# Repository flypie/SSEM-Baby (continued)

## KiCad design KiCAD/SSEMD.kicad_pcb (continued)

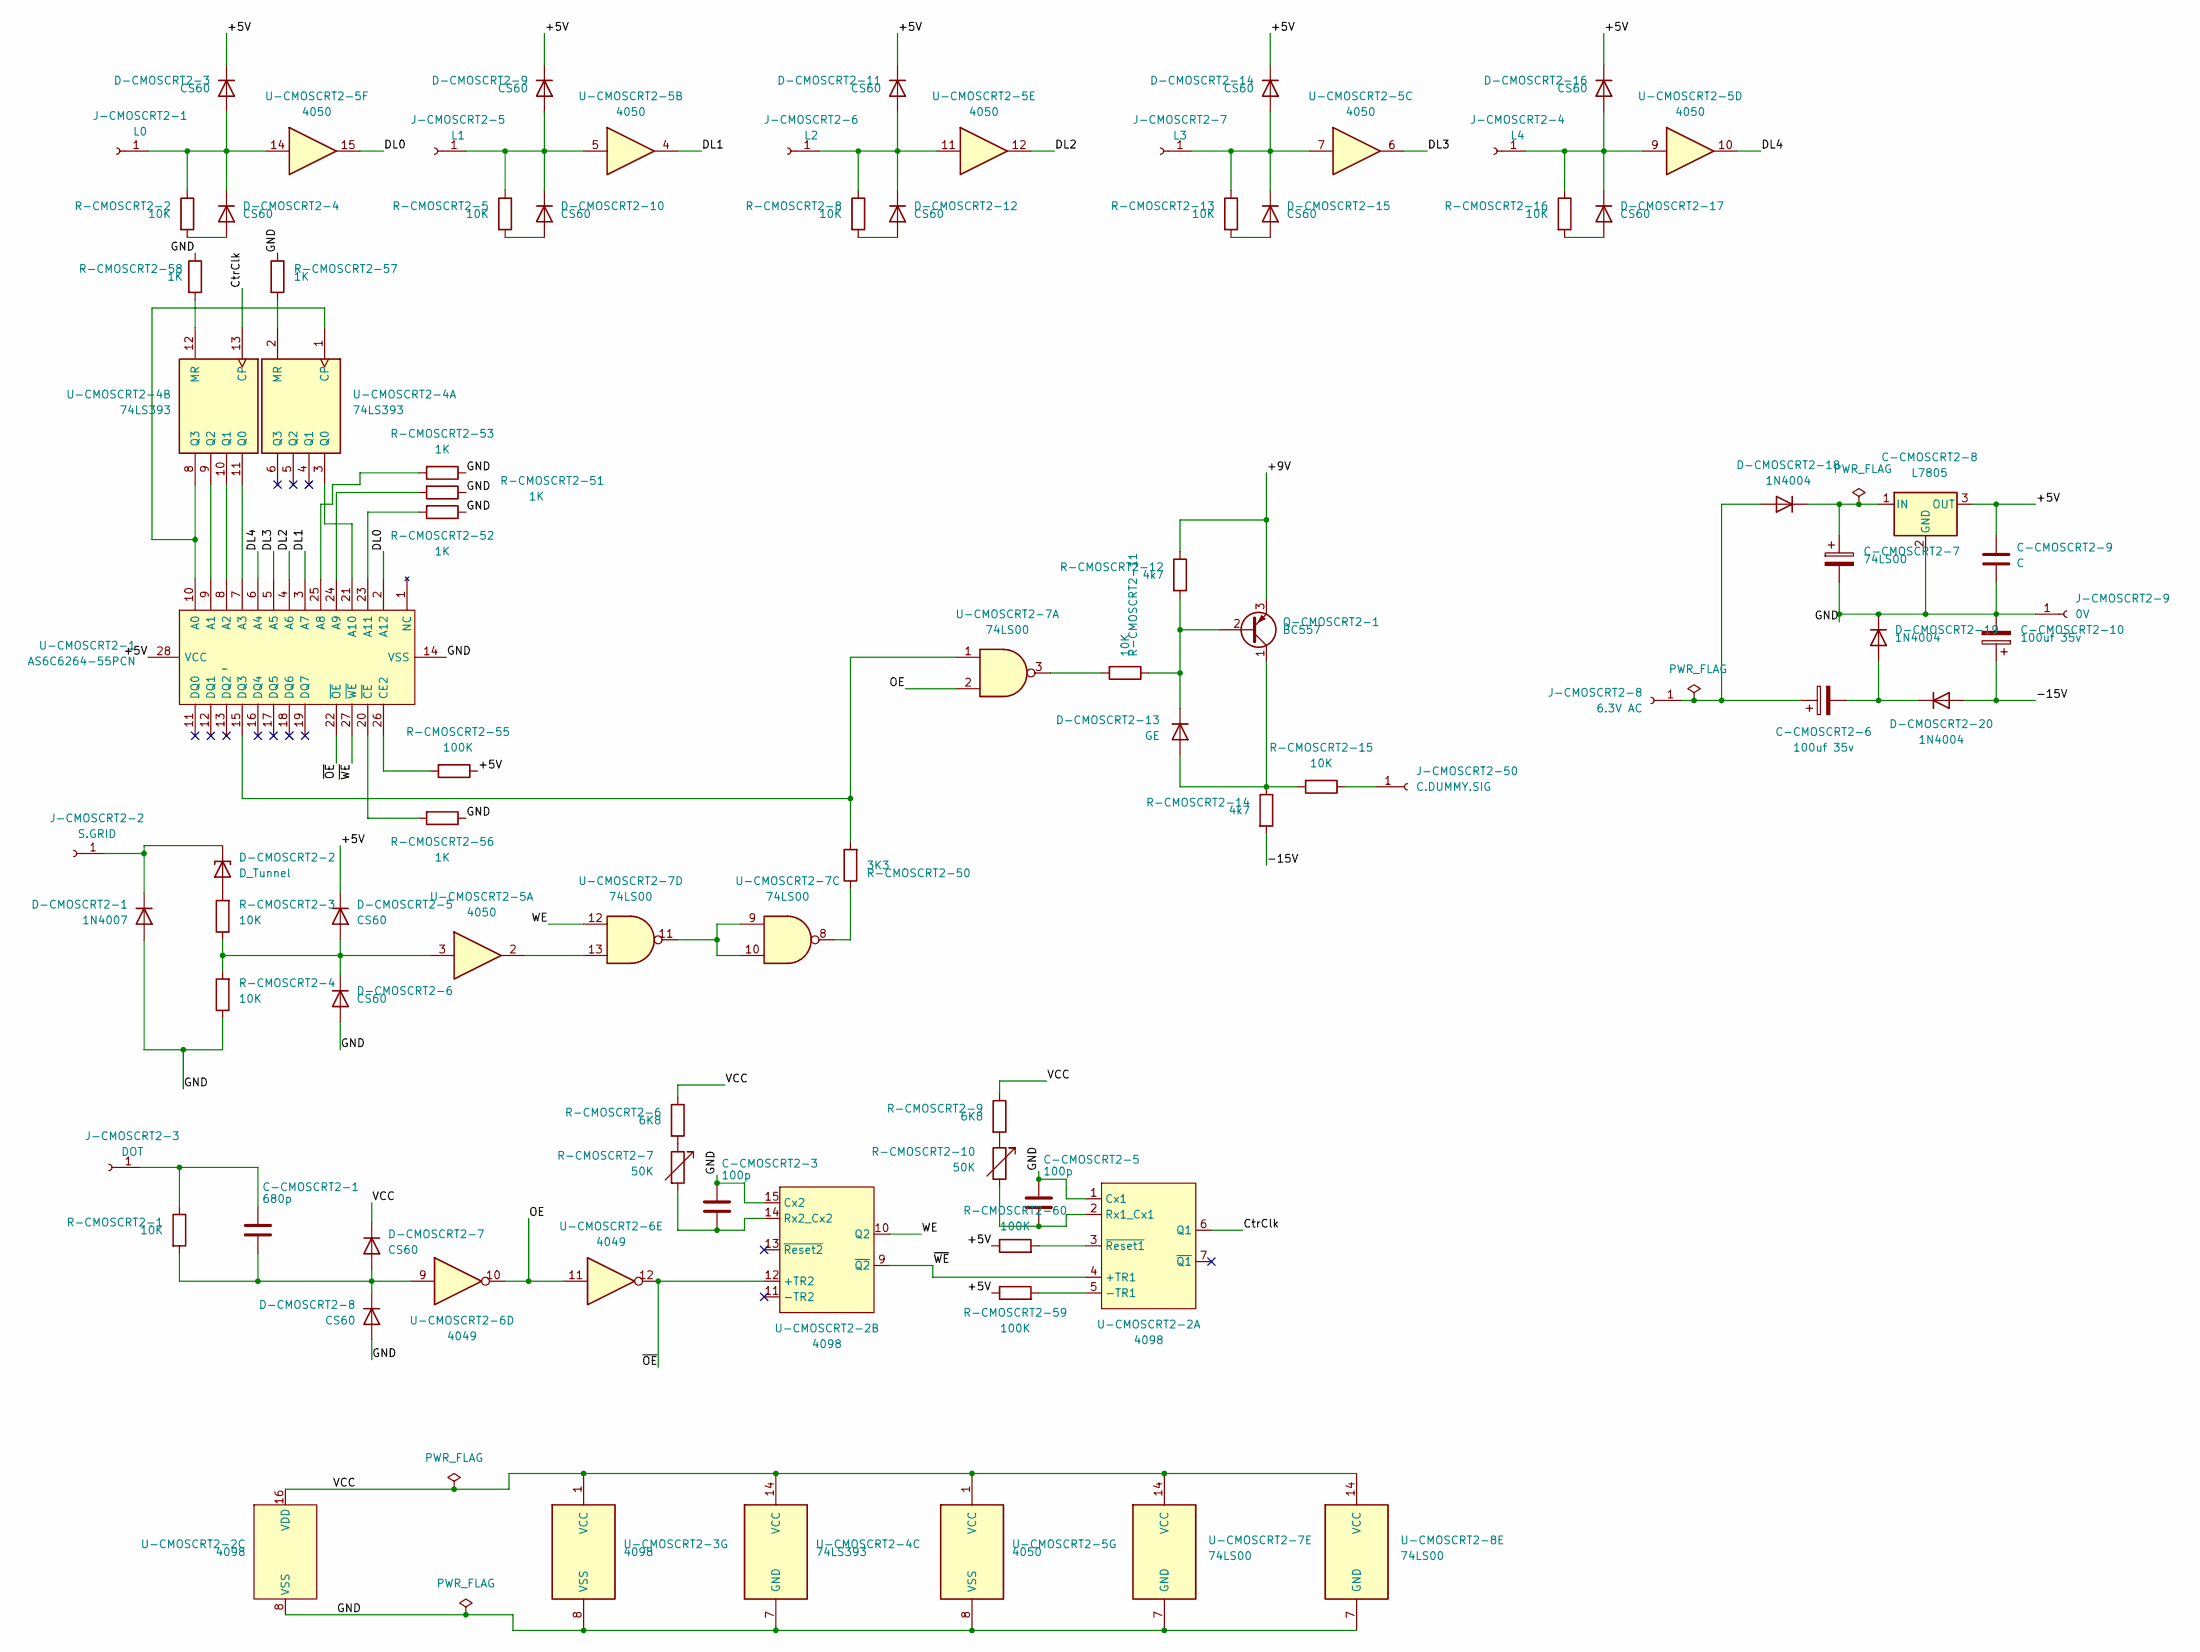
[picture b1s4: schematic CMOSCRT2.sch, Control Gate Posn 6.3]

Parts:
C-CMOSCRT2-1: 680p; C_Disc_D7.5mm_W5.0mm_P5.00mm
C-CMOSCRT2-3, C-CMOSCRT2-5: 100p; C_Disc_D7.5mm_W5.0mm_P5.00mm
C-CMOSCRT2-6, C-CMOSCRT2-10: 100uf 35v; CP_Radial_D5.0mm_P2.50mm
C-CMOSCRT2-7: 74LS00; CP_Radial_D5.0mm_P2.50mm
C-CMOSCRT2-8: L7805; TO-220-3_Vertical
C-CMOSCRT2-9: C; C_Disc_D3.8mm_W2.6mm_P2.50mm
D-CMOSCRT2-1: 1N4007; D_DO-41_SOD81_P10.16mm_Horizontal
D-CMOSCRT2-2: D_Tunnel; D_DO-41_SOD81_P10.16mm_Horizontal
D-CMOSCRT2-3, D-CMOSCRT2-4, D-CMOSCRT2-5, D-CMOSCRT2-6, D-CMOSCRT2-7, D-CMOSCRT2-8, D-CMOSCRT2-9, D-CMOSCRT2-10, D-CMOSCRT2-11, D-CMOSCRT2-12, D-CMOSCRT2-14, D-CMOSCRT2-15, D-CMOSCRT2-16, D-CMOSCRT2-17: CS60; D_DO-41_SOD81_P10.16mm_Horizontal
D-CMOSCRT2-13: GE; D_DO-41_SOD81_P10.16mm_Horizontal
D-CMOSCRT2-18, D-CMOSCRT2-19, D-CMOSCRT2-20: 1N4004; D_DO-41_SOD81_P10.16mm_Horizontal
J-CMOSCRT2-1: L0; 242431
J-CMOSCRT2-2: S.GRID; 242431
J-CMOSCRT2-3: DOT; 242431
J-CMOSCRT2-4: L4; 242431
J-CMOSCRT2-5: L1; 242431
J-CMOSCRT2-6: L2; 242431
J-CMOSCRT2-7: L3; 242431
J-CMOSCRT2-8: 6.3V AC; 242431
J-CMOSCRT2-9: 0V; 242431
J-CMOSCRT2-50: C.DUMMY.SIG; 242431
Q-CMOSCRT2-1: BC557; TO-92_Inline
R-CMOSCRT2-1, R-CMOSCRT2-2, R-CMOSCRT2-3, R-CMOSCRT2-4, R-CMOSCRT2-5, R-CMOSCRT2-8, R-CMOSCRT2-11, R-CMOSCRT2-13, R-CMOSCRT2-15, R-CMOSCRT2-16: 10K; R_Axial_DIN0516_L15.5mm_D5.0mm_P5.08mm_Vertical
R-CMOSCRT2-6, R-CMOSCRT2-9: 6K8; R_Axial_DIN0516_L15.5mm_D5.0mm_P5.08mm_Vertical
R-CMOSCRT2-7, R-CMOSCRT2-10: 50K; Potentiometer_Omeg_PC16BU_Vertical
R-CMOSCRT2-12, R-CMOSCRT2-14: 4k7; R_Axial_DIN0516_L15.5mm_D5.0mm_P5.08mm_Vertical
R-CMOSCRT2-50: 3K3; R_Axial_DIN0516_L15.5mm_D5.0mm_P5.08mm_Vertical
R-CMOSCRT2-51, R-CMOSCRT2-52, R-CMOSCRT2-53, R-CMOSCRT2-56, R-CMOSCRT2-57, R-CMOSCRT2-58: 1K; R_Axial_DIN0516_L15.5mm_D5.0mm_P5.08mm_Vertical
R-CMOSCRT2-55, R-CMOSCRT2-59, R-CMOSCRT2-60: 100K; R_Axial_DIN0516_L15.5mm_D5.0mm_P5.08mm_Vertical
U-CMOSCRT2-1: AS6C6264-55PCN; DIP1524W51P254L3632H394Q28N; Manufacturer_Part_Number AS6C6264-55PCN; Mouser Part Number 913-AS6C6264-55PCN
U-CMOSCRT2-2: 4098; DIP-16_W7.62mm
U-CMOSCRT2-3: 4098; DIP-14_W7.62mm
U-CMOSCRT2-4: 74LS393; DIP-14_W7.62mm
U-CMOSCRT2-5: 4050; DIP-16_W7.62mm
U-CMOSCRT2-6: 4049; DIP-14_W7.62mm
U-CMOSCRT2-7, U-CMOSCRT2-8: 74LS00; DIP-14_W7.62mm

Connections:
/CMOSCRT2/+5V: C-CMOSCRT2-8.3 (OUT), C-CMOSCRT2-9.1, D-CMOSCRT2-3.1 (K), D-CMOSCRT2-5.1 (K), D-CMOSCRT2-9.1 (K), D-CMOSCRT2-11.1 (K), D-CMOSCRT2-14.1 (K), D-CMOSCRT2-16.1 (K), R-CMOSCRT2-55.1, R-CMOSCRT2-59.1, R-CMOSCRT2-60.1, U-CMOSCRT2-1.28 (VCC)
/CMOSCRT2/+9V: Q-CMOSCRT2-1.3 (E), R-CMOSCRT2-12.1
/CMOSCRT2/-15V: C-CMOSCRT2-10.1, D-CMOSCRT2-20.2 (A), R-CMOSCRT2-14.2
/CMOSCRT2/CtrClk: U-CMOSCRT2-2.6 (Q1), U-CMOSCRT2-4.13 (CP)
/CMOSCRT2/DL0: U-CMOSCRT2-1.2 (A12), U-CMOSCRT2-5.15
/CMOSCRT2/DL1: U-CMOSCRT2-1.3 (A7), U-CMOSCRT2-5.4
/CMOSCRT2/DL2: U-CMOSCRT2-1.4 (A6), U-CMOSCRT2-5.12
/CMOSCRT2/DL3: U-CMOSCRT2-1.5 (A5), U-CMOSCRT2-5.6
/CMOSCRT2/DL4: U-CMOSCRT2-1.6 (A4), U-CMOSCRT2-5.10
/CMOSCRT2/GND: C-CMOSCRT2-3.1, C-CMOSCRT2-5.1, C-CMOSCRT2-7.2, C-CMOSCRT2-8.2 (GND), C-CMOSCRT2-9.2, C-CMOSCRT2-10.2, D-CMOSCRT2-1.2 (A), D-CMOSCRT2-6.2 (A), D-CMOSCRT2-8.2 (A), D-CMOSCRT2-19.1 (K), J-CMOSCRT2-9.1, R-CMOSCRT2-4.1, R-CMOSCRT2-51.1, R-CMOSCRT2-52.1, R-CMOSCRT2-53.1, R-CMOSCRT2-56.1, R-CMOSCRT2-57.1, R-CMOSCRT2-58.1, U-CMOSCRT2-1.14 (VSS), U-CMOSCRT2-2.1 (Cx1), U-CMOSCRT2-2.8 (VSS), U-CMOSCRT2-2.15 (Cx2), U-CMOSCRT2-3.8 (VSS), U-CMOSCRT2-4.7 (GND), U-CMOSCRT2-5.8 (VSS), U-CMOSCRT2-7.7 (GND), U-CMOSCRT2-8.7 (GND)
/CMOSCRT2/OE: U-CMOSCRT2-6.10, U-CMOSCRT2-6.11, U-CMOSCRT2-7.2
/CMOSCRT2/VCC: D-CMOSCRT2-7.1 (K), R-CMOSCRT2-6.1, R-CMOSCRT2-9.1, U-CMOSCRT2-2.16 (VDD), U-CMOSCRT2-3.1 (VCC), U-CMOSCRT2-4.14 (VCC), U-CMOSCRT2-5.1 (VCC), U-CMOSCRT2-7.14 (VCC), U-CMOSCRT2-8.14 (VCC)
/CMOSCRT2/WE: U-CMOSCRT2-2.10 (Q2), U-CMOSCRT2-7.12
/CMOSCRT2/~OE: U-CMOSCRT2-1.22 (~OE), U-CMOSCRT2-2.12 (+TR2), U-CMOSCRT2-6.12
/CMOSCRT2/~WE: U-CMOSCRT2-1.27 (~WE), U-CMOSCRT2-2.4 (+TR1), U-CMOSCRT2-2.9 (~Q2)
unnamed: C-CMOSCRT2-1.1, J-CMOSCRT2-3.1, R-CMOSCRT2-1.1
unnamed: C-CMOSCRT2-1.2, D-CMOSCRT2-7.2 (A), D-CMOSCRT2-8.1 (K), R-CMOSCRT2-1.2, U-CMOSCRT2-6.9
unnamed: C-CMOSCRT2-3.2, R-CMOSCRT2-7.2, U-CMOSCRT2-2.14 (Rx2_Cx2)
unnamed: C-CMOSCRT2-5.2, R-CMOSCRT2-10.2, U-CMOSCRT2-2.2 (Rx1_Cx1)
unnamed: C-CMOSCRT2-6.1, D-CMOSCRT2-18.2 (A), J-CMOSCRT2-8.1
unnamed: C-CMOSCRT2-6.2, D-CMOSCRT2-19.2 (A), D-CMOSCRT2-20.1 (K)
unnamed: C-CMOSCRT2-7.1, C-CMOSCRT2-8.1 (IN), D-CMOSCRT2-18.1 (K)
unnamed: D-CMOSCRT2-1.1 (K), D-CMOSCRT2-2.1 (K), J-CMOSCRT2-2.1
unnamed: D-CMOSCRT2-2.2 (A), R-CMOSCRT2-3.2
unnamed: D-CMOSCRT2-3.2 (A), D-CMOSCRT2-4.1 (K), J-CMOSCRT2-1.1, R-CMOSCRT2-2.1, U-CMOSCRT2-5.14
unnamed: D-CMOSCRT2-4.2 (A), R-CMOSCRT2-2.2
unnamed: D-CMOSCRT2-5.2 (A), D-CMOSCRT2-6.1 (K), R-CMOSCRT2-3.1, R-CMOSCRT2-4.2, U-CMOSCRT2-5.3
unnamed: D-CMOSCRT2-9.2 (A), D-CMOSCRT2-10.1 (K), J-CMOSCRT2-5.1, R-CMOSCRT2-5.1, U-CMOSCRT2-5.5
unnamed: D-CMOSCRT2-10.2 (A), R-CMOSCRT2-5.2
unnamed: D-CMOSCRT2-11.2 (A), D-CMOSCRT2-12.1 (K), J-CMOSCRT2-6.1, R-CMOSCRT2-8.1, U-CMOSCRT2-5.11
unnamed: D-CMOSCRT2-12.2 (A), R-CMOSCRT2-8.2
unnamed: D-CMOSCRT2-13.1 (K), Q-CMOSCRT2-1.2 (B), R-CMOSCRT2-11.1, R-CMOSCRT2-12.2
unnamed: D-CMOSCRT2-13.2 (A), Q-CMOSCRT2-1.1 (C), R-CMOSCRT2-14.1, R-CMOSCRT2-15.2
unnamed: D-CMOSCRT2-14.2 (A), D-CMOSCRT2-15.1 (K), J-CMOSCRT2-7.1, R-CMOSCRT2-13.1, U-CMOSCRT2-5.7
unnamed: D-CMOSCRT2-15.2 (A), R-CMOSCRT2-13.2
unnamed: D-CMOSCRT2-16.2 (A), D-CMOSCRT2-17.1 (K), J-CMOSCRT2-4.1, R-CMOSCRT2-16.1, U-CMOSCRT2-5.9
unnamed: D-CMOSCRT2-17.2 (A), R-CMOSCRT2-16.2
unnamed: J-CMOSCRT2-50.1, R-CMOSCRT2-15.1
unnamed: R-CMOSCRT2-6.2, R-CMOSCRT2-7.1
unnamed: R-CMOSCRT2-9.2, R-CMOSCRT2-10.1
unnamed: R-CMOSCRT2-11.2, U-CMOSCRT2-7.3
unnamed: R-CMOSCRT2-50.1, U-CMOSCRT2-7.8
unnamed: R-CMOSCRT2-50.2, U-CMOSCRT2-1.15 (DQ3), U-CMOSCRT2-7.1
unnamed: R-CMOSCRT2-51.2, U-CMOSCRT2-1.24 (A9)
unnamed: R-CMOSCRT2-52.2, U-CMOSCRT2-1.23 (A11)
unnamed: R-CMOSCRT2-53.2, U-CMOSCRT2-1.25 (A8)
unnamed: R-CMOSCRT2-55.2, U-CMOSCRT2-1.26 (CE2)
unnamed: R-CMOSCRT2-56.2, U-CMOSCRT2-1.20 (~CE)
unnamed: R-CMOSCRT2-57.2, U-CMOSCRT2-4.2 (MR)
unnamed: R-CMOSCRT2-58.2, U-CMOSCRT2-4.12 (MR)
unnamed: R-CMOSCRT2-59.2, U-CMOSCRT2-2.5 (-TR1)
unnamed: R-CMOSCRT2-60.2, U-CMOSCRT2-2.3 (~Reset1)
unnamed: U-CMOSCRT2-1.7 (A3), U-CMOSCRT2-4.11 (Q0)
unnamed: U-CMOSCRT2-1.8 (A2), U-CMOSCRT2-4.10 (Q1)
unnamed: U-CMOSCRT2-1.9 (A1), U-CMOSCRT2-4.9 (Q2)
unnamed: U-CMOSCRT2-1.10 (A0), U-CMOSCRT2-4.1 (CP), U-CMOSCRT2-4.8 (Q3)
unnamed: U-CMOSCRT2-1.21 (A10), U-CMOSCRT2-4.3 (Q0)
unnamed: U-CMOSCRT2-5.2, U-CMOSCRT2-7.13
unnamed: U-CMOSCRT2-7.9, U-CMOSCRT2-7.10, U-CMOSCRT2-7.11

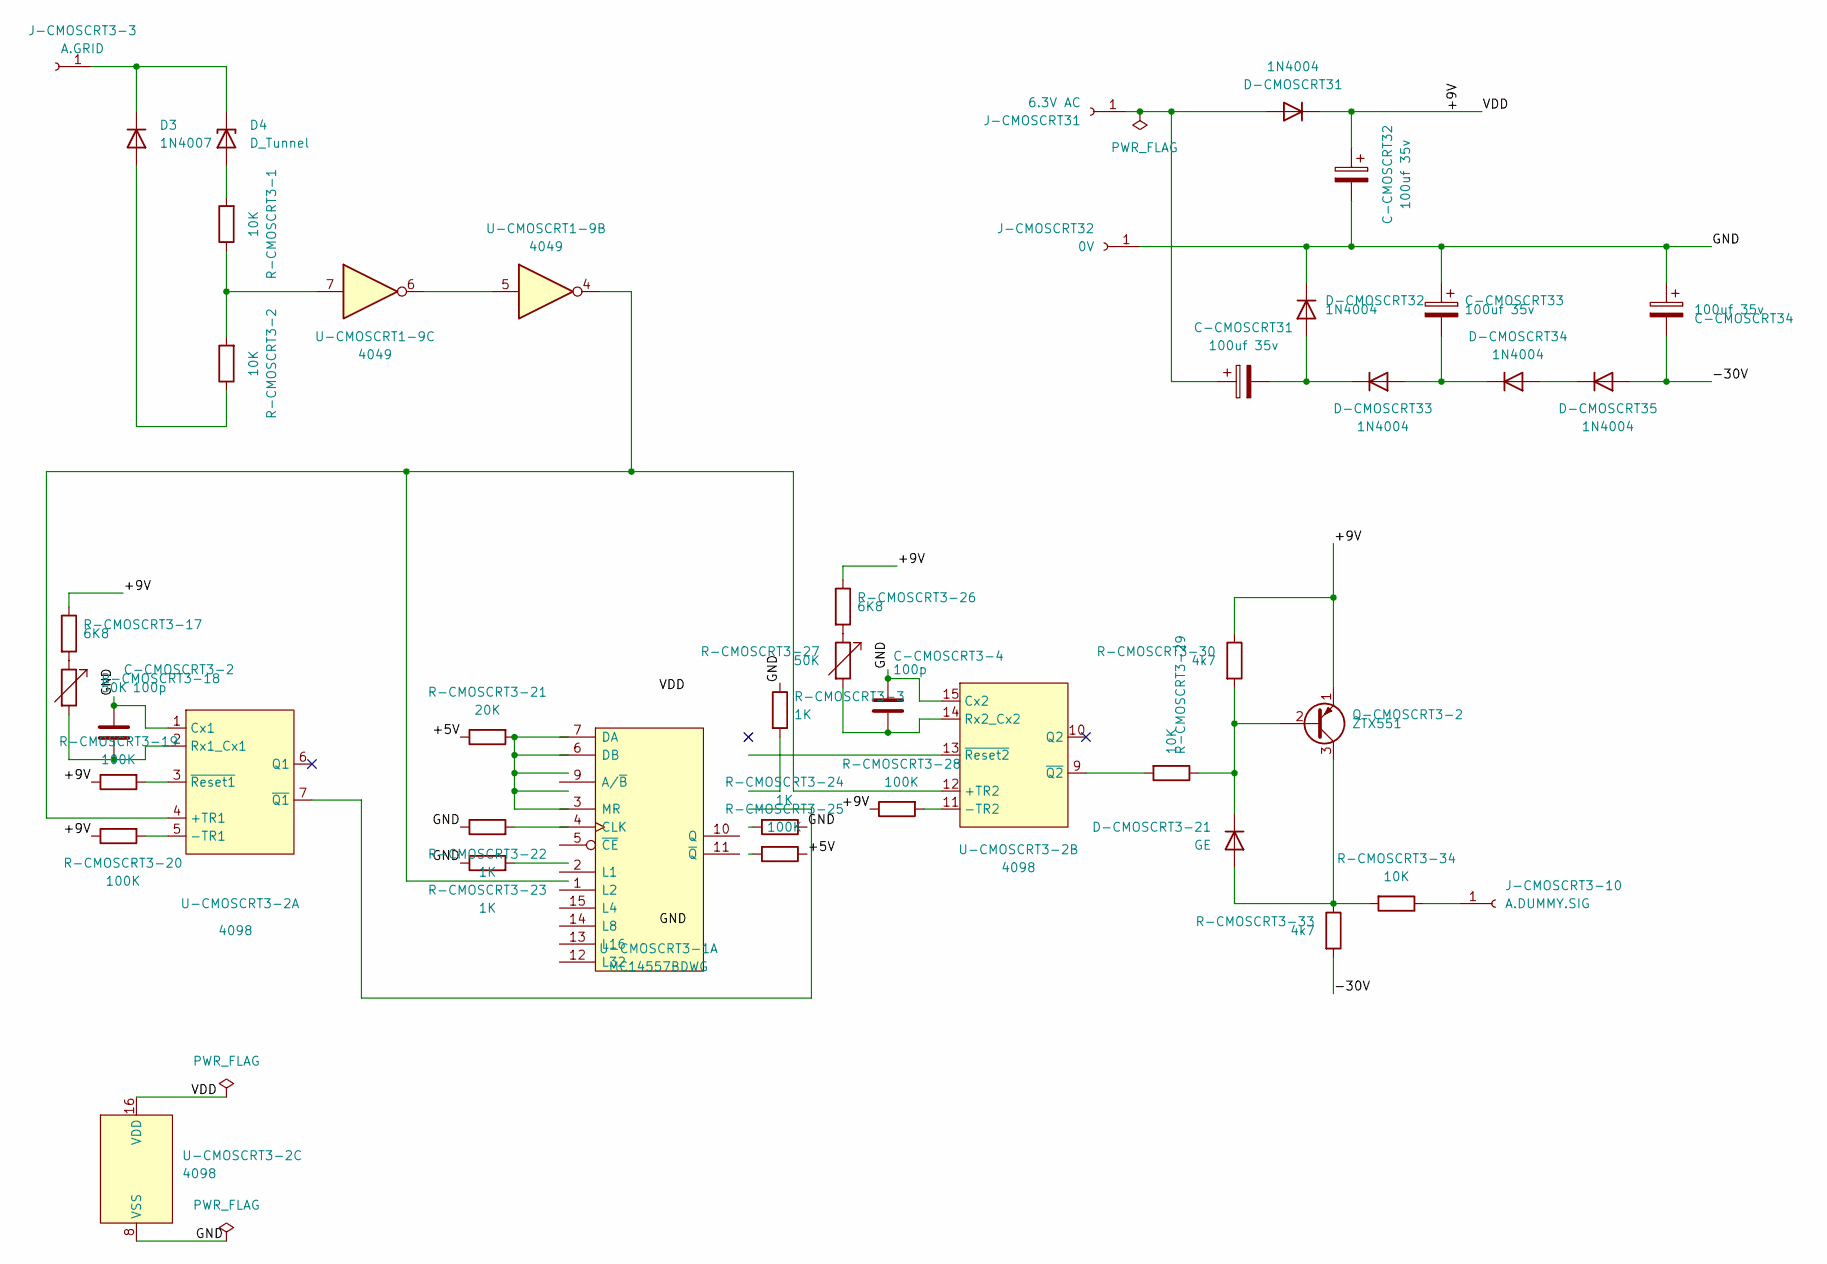
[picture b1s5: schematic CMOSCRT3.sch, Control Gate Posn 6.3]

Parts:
C-CMOSCRT3-2, C-CMOSCRT3-4: 100p; C_Disc_D7.5mm_W5.0mm_P5.00mm
C-CMOSCRT31, C-CMOSCRT32, C-CMOSCRT33, C-CMOSCRT34: 100uf 35v; CP_Radial_D7.5mm_P2.50mm
D3: 1N4007; D_DO-41_SOD81_P10.16mm_Horizontal
D4: D_Tunnel; D_DO-201_P15.24mm_Horizontal
D-CMOSCRT3-21: GE; D_DO-41_SOD81_P10.16mm_Horizontal
D-CMOSCRT31, D-CMOSCRT32, D-CMOSCRT33, D-CMOSCRT34, D-CMOSCRT35: 1N4004; D_DO-41_SOD81_P10.16mm_Horizontal
J-CMOSCRT3-3: A.GRID; 242431
J-CMOSCRT3-10: A.DUMMY.SIG; 242431
J-CMOSCRT31: 6.3V AC; 242431
J-CMOSCRT32: 0V; 242431
Q-CMOSCRT3-2: ZTX551; TO-92_Inline
R-CMOSCRT3-1, R-CMOSCRT3-2, R-CMOSCRT3-29, R-CMOSCRT3-34: 10K; R_Axial_DIN0516_L15.5mm_D5.0mm_P5.08mm_Vertical
R-CMOSCRT3-3, R-CMOSCRT3-22, R-CMOSCRT3-23, R-CMOSCRT3-24: 1K; R_Axial_DIN0516_L15.5mm_D5.0mm_P5.08mm_Vertical
R-CMOSCRT3-17, R-CMOSCRT3-26: 6K8; R_Axial_DIN0516_L15.5mm_D5.0mm_P5.08mm_Vertical
R-CMOSCRT3-18: 50K; Potentiometer_Omeg_PC16BU_Vertical
R-CMOSCRT3-19, R-CMOSCRT3-20, R-CMOSCRT3-25, R-CMOSCRT3-28: 100K; R_Axial_DIN0516_L15.5mm_D5.0mm_P5.08mm_Vertical
R-CMOSCRT3-21: 20K; R_Axial_DIN0516_L15.5mm_D5.0mm_P5.08mm_Vertical
R-CMOSCRT3-27: 50K; R_Axial_DIN0516_L15.5mm_D5.0mm_P5.08mm_Vertical
R-CMOSCRT3-30, R-CMOSCRT3-33: 4k7; R_Axial_DIN0516_L15.5mm_D5.0mm_P5.08mm_Vertical
U-CMOSCRT1-9: 4049; DIP-14_W7.62mm
U-CMOSCRT3-1: MC14557BDWG; DIP-16_W7.62mm; Manufacturer_Part_Number MC14557BDWG; Mouser Part Number 863-MC14557BDWG
U-CMOSCRT3-2: 4098; DIP-16_W7.62mm

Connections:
/CMOSCRT3/+5V: R-CMOSCRT3-21.1, R-CMOSCRT3-25.1
/CMOSCRT3/+9V: C-CMOSCRT32.1, D-CMOSCRT31.1 (K), Q-CMOSCRT3-2.1 (E), R-CMOSCRT3-17.1, R-CMOSCRT3-19.1, R-CMOSCRT3-20.1, R-CMOSCRT3-26.1, R-CMOSCRT3-28.1, R-CMOSCRT3-30.1, U-CMOSCRT3-2.16 (VDD)
/CMOSCRT3/-30V: C-CMOSCRT34.2, D-CMOSCRT35.2 (A), R-CMOSCRT3-33.2
/CMOSCRT3/GND: C-CMOSCRT3-2.1, C-CMOSCRT3-4.1, C-CMOSCRT32.2, C-CMOSCRT33.1, C-CMOSCRT34.1, D-CMOSCRT32.1 (K), J-CMOSCRT32.1, R-CMOSCRT3-3.1, R-CMOSCRT3-22.1, R-CMOSCRT3-23.1, R-CMOSCRT3-24.1, U-CMOSCRT3-2.1 (Cx1), U-CMOSCRT3-2.8 (VSS), U-CMOSCRT3-2.15 (Cx2)
unnamed: C-CMOSCRT3-2.2, R-CMOSCRT3-18.2, U-CMOSCRT3-2.2 (Rx1_Cx1)
unnamed: C-CMOSCRT3-4.2, R-CMOSCRT3-27.2, U-CMOSCRT3-2.14 (Rx2_Cx2)
unnamed: C-CMOSCRT31.1, D-CMOSCRT31.2 (A), J-CMOSCRT31.1
unnamed: C-CMOSCRT31.2, D-CMOSCRT32.2 (A), D-CMOSCRT33.1 (K)
unnamed: C-CMOSCRT33.2, D-CMOSCRT33.2 (A), D-CMOSCRT34.1 (K)
unnamed: D3.1 (K), D4.1 (K), J-CMOSCRT3-3.1
unnamed: D3.2 (A), R-CMOSCRT3-2.1
unnamed: D4.2 (A), R-CMOSCRT3-1.2
unnamed: D-CMOSCRT3-21.1 (K), Q-CMOSCRT3-2.2 (B), R-CMOSCRT3-29.1, R-CMOSCRT3-30.2
unnamed: D-CMOSCRT3-21.2 (A), Q-CMOSCRT3-2.3 (C), R-CMOSCRT3-33.1, R-CMOSCRT3-34.2
unnamed: D-CMOSCRT34.2 (A), D-CMOSCRT35.1 (K)
unnamed: J-CMOSCRT3-10.1, R-CMOSCRT3-34.1
unnamed: R-CMOSCRT3-1.1, R-CMOSCRT3-2.2, U-CMOSCRT1-9.7
unnamed: R-CMOSCRT3-17.2, R-CMOSCRT3-18.1
unnamed: R-CMOSCRT3-19.2, U-CMOSCRT3-2.3 (~Reset1)
unnamed: R-CMOSCRT3-20.2, U-CMOSCRT3-2.5 (-TR1)
unnamed: R-CMOSCRT3-26.2, R-CMOSCRT3-27.1
unnamed: R-CMOSCRT3-28.2, U-CMOSCRT3-2.11 (-TR2)
unnamed: R-CMOSCRT3-29.2, U-CMOSCRT3-2.9 (~Q2)
unnamed: U-CMOSCRT1-9.4, U-CMOSCRT3-2.4 (+TR1), U-CMOSCRT3-2.12 (+TR2)
unnamed: U-CMOSCRT1-9.5, U-CMOSCRT1-9.6

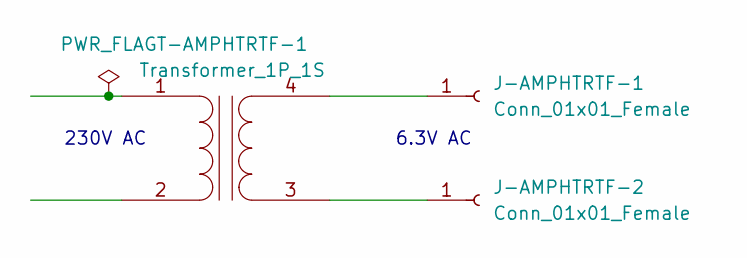
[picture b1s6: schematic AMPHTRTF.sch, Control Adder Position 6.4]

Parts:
J-AMPHTRTF-1, J-AMPHTRTF-2: Conn_01x01_Female; Banana_Jack_1Pin
T-AMPHTRTF-1: Transformer_1P_1S; FP12950

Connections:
unnamed: J-AMPHTRTF-1.1, T-AMPHTRTF-1.4 (SB)
unnamed: J-AMPHTRTF-2.1, T-AMPHTRTF-1.3 (SA)

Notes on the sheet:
6.3V AC
230V AC

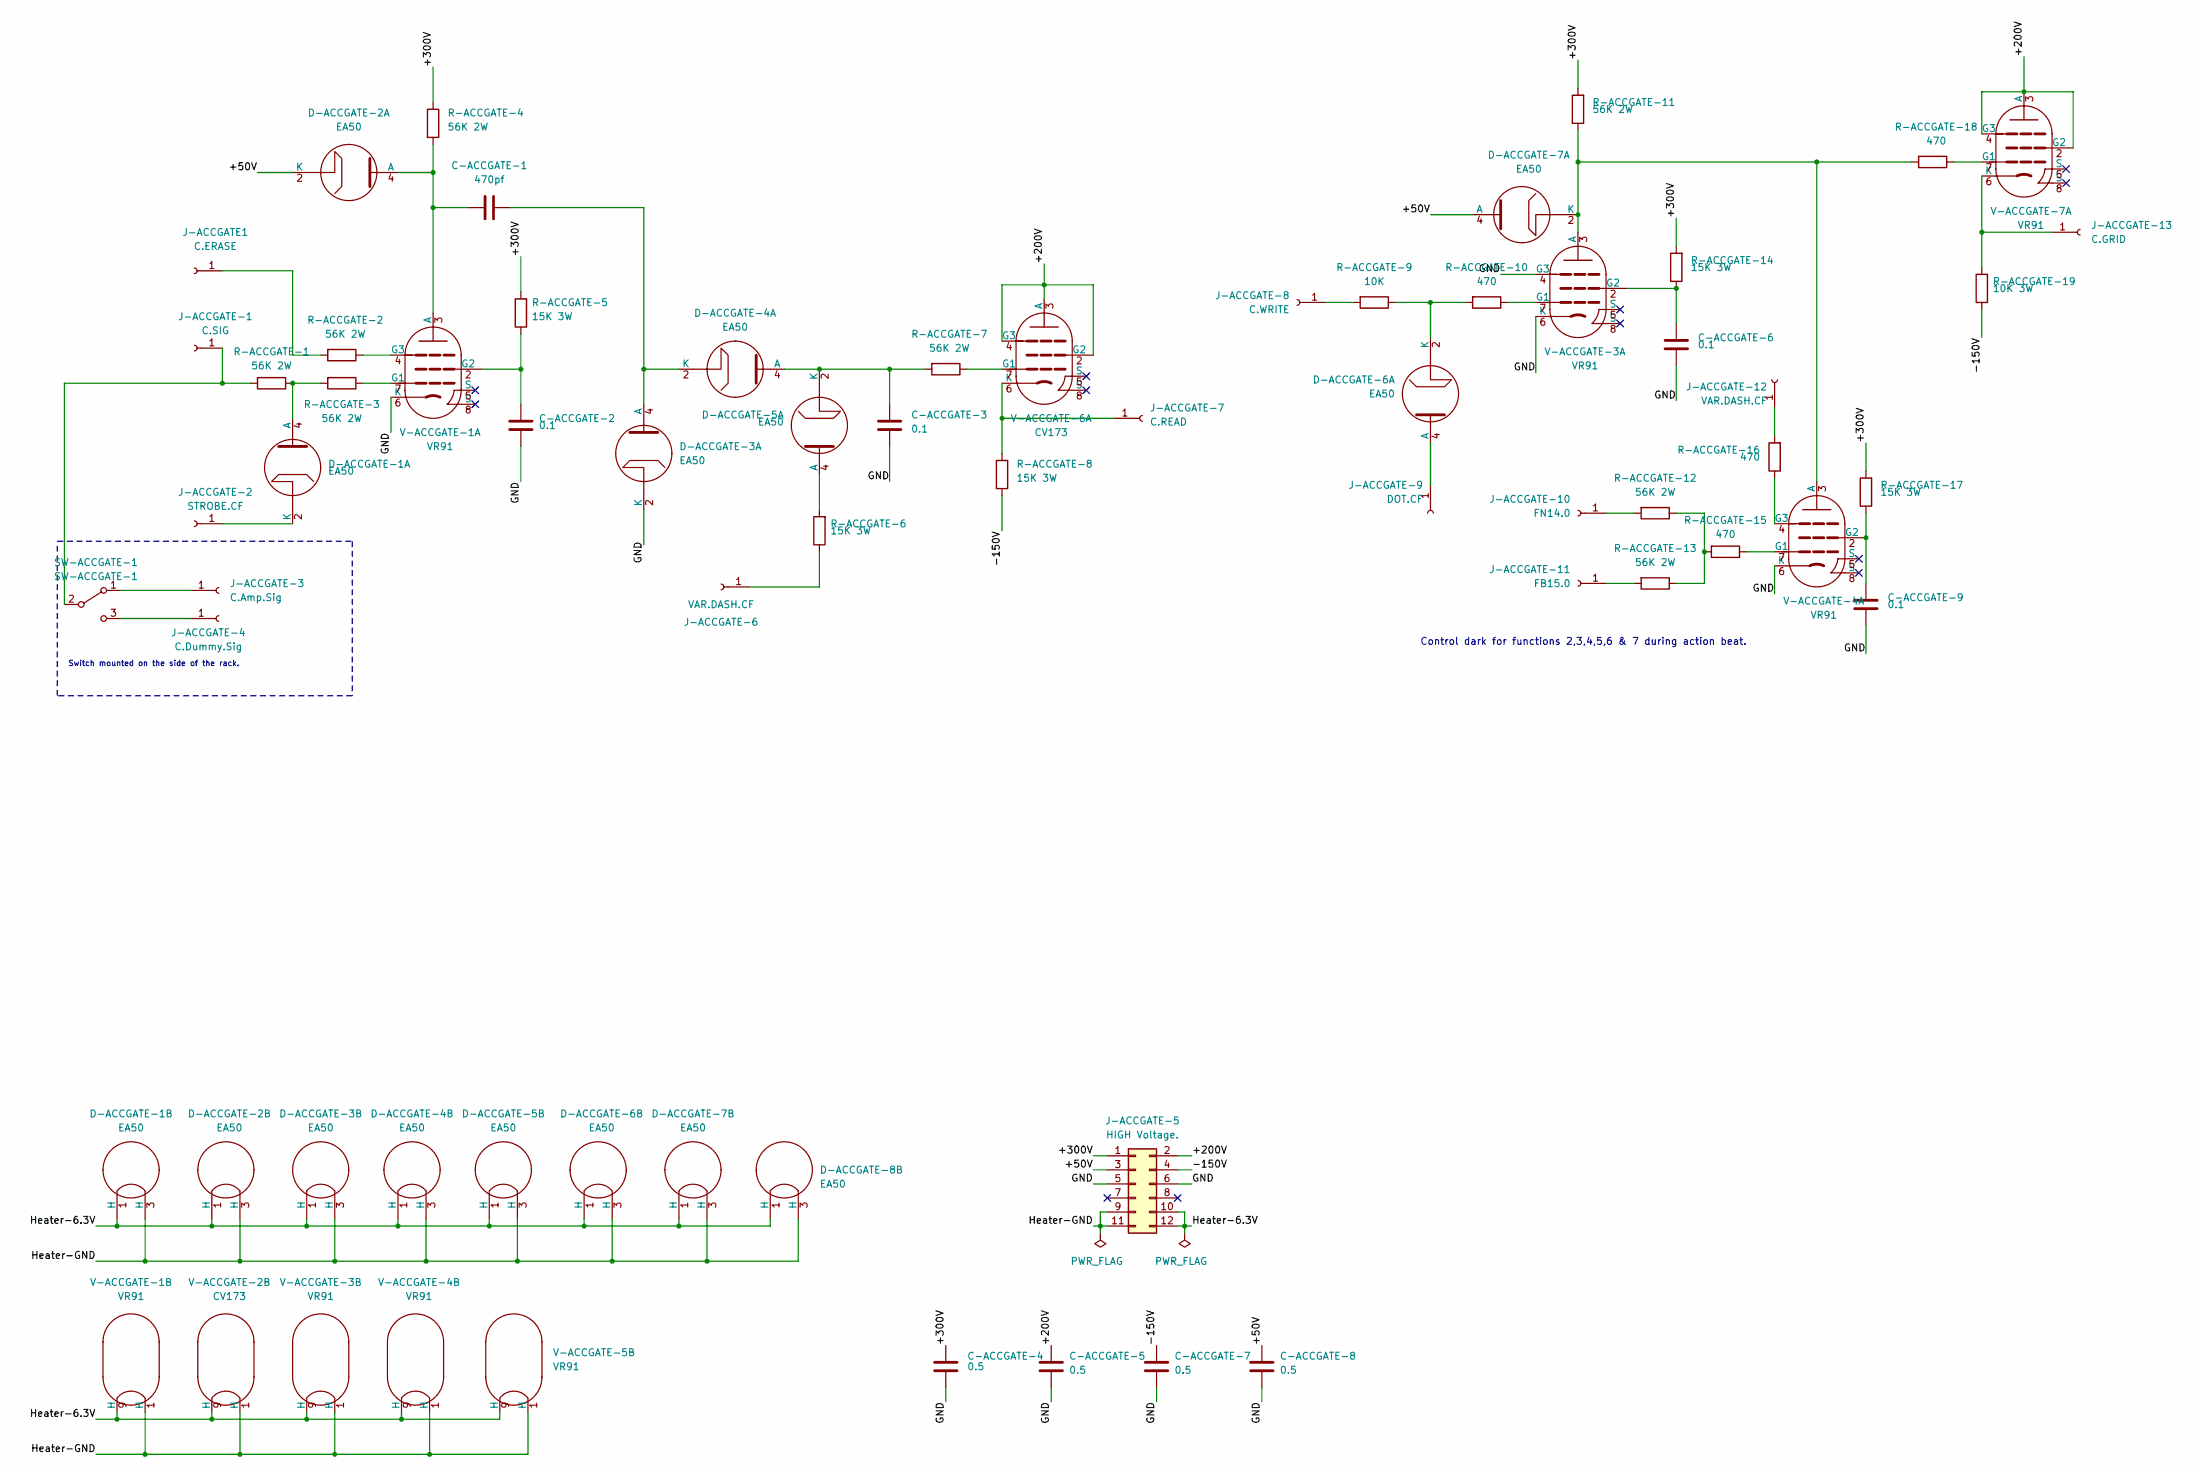
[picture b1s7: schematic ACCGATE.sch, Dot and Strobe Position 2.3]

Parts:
C-ACCGATE-1: 470pf; C_Disc_D7.5mm_W5.0mm_P5.00mm
C-ACCGATE-2, C-ACCGATE-3, C-ACCGATE-6, C-ACCGATE-9: 0.1; C_Disc_D7.5mm_W5.0mm_P5.00mm
C-ACCGATE-4, C-ACCGATE-5, C-ACCGATE-7, C-ACCGATE-8: 0.5; C_Disc_D7.5mm_W5.0mm_P5.00mm
D-ACCGATE-1, D-ACCGATE-2, D-ACCGATE-3, D-ACCGATE-4, D-ACCGATE-5, D-ACCGATE-6, D-ACCGATE-7, D-ACCGATE-8: EA50; Valve_B3G
J-ACCGATE1: C.ERASE; 242431
J-ACCGATE-1: C.SIG; 242431
J-ACCGATE-2: STROBE.CF; 242431
J-ACCGATE-3: C.Amp.Sig; 242431
J-ACCGATE-4: C.Dummy.Sig; 242431
J-ACCGATE-5: HIGH Voltage.; TE_MATE-N-LOK_1-770972-x_2x06_P4.14mm_Horizontal
J-ACCGATE-6, J-ACCGATE-12: VAR.DASH.CF; 242431
J-ACCGATE-7: C.READ; 242431
J-ACCGATE-8: C.WRITE; 242431
J-ACCGATE-9: DOT.CF; 242431
J-ACCGATE-10: FN14.0; 242431
J-ACCGATE-11: FB15.0; 242431
J-ACCGATE-13: C.GRID; 242431
R-ACCGATE-1, R-ACCGATE-2, R-ACCGATE-3, R-ACCGATE-4, R-ACCGATE-7, R-ACCGATE-11, R-ACCGATE-12, R-ACCGATE-13: 56K 2W; R_Axial_DIN0516_L15.5mm_D5.0mm_P5.08mm_Vertical
R-ACCGATE-5, R-ACCGATE-6, R-ACCGATE-8, R-ACCGATE-14, R-ACCGATE-17: 15K 3W; R_Axial_DIN0516_L15.5mm_D5.0mm_P5.08mm_Vertical
R-ACCGATE-9: 10K; R_Axial_DIN0516_L15.5mm_D5.0mm_P5.08mm_Vertical
R-ACCGATE-10, R-ACCGATE-15, R-ACCGATE-16, R-ACCGATE-18: 470; R_Axial_DIN0516_L15.5mm_D5.0mm_P5.08mm_Vertical
R-ACCGATE-19: 10K 3W; R_Axial_DIN0516_L15.5mm_D5.0mm_P5.08mm_Vertical
SW-ACCGATE-1: SW-ACCGATE-1; M2011SS1W03
V-ACCGATE-1, V-ACCGATE-3, V-ACCGATE-4, V-ACCGATE-5, V-ACCGATE-7: VR91; Valve_9Loctal
V-ACCGATE-2, V-ACCGATE-6: CV173; Valve_9Loctal

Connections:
/ACCGATE/+50V: C-ACCGATE-8.1, D-ACCGATE-2.2 (K), D-ACCGATE-7.4 (A), J-ACCGATE-5.3
/ACCGATE/+200V: C-ACCGATE-5.1, J-ACCGATE-5.2, V-ACCGATE-6.2 (G2), V-ACCGATE-6.3 (A), V-ACCGATE-6.4 (G3), V-ACCGATE-7.2 (G2), V-ACCGATE-7.3 (A), V-ACCGATE-7.4 (G3)
/ACCGATE/+300V: C-ACCGATE-4.1, J-ACCGATE-5.1, R-ACCGATE-4.1, R-ACCGATE-5.2, R-ACCGATE-11.2, R-ACCGATE-14.2, R-ACCGATE-17.2
/ACCGATE/-150V: C-ACCGATE-7.2, J-ACCGATE-5.4, R-ACCGATE-8.1, R-ACCGATE-19.1
/ACCGATE/GND: C-ACCGATE-2.2, C-ACCGATE-3.2, C-ACCGATE-4.2, C-ACCGATE-5.2, C-ACCGATE-6.2, C-ACCGATE-7.1, C-ACCGATE-8.2, C-ACCGATE-9.2, D-ACCGATE-3.2 (K), J-ACCGATE-5.5, J-ACCGATE-5.6, V-ACCGATE-1.6 (K), V-ACCGATE-3.4 (G3), V-ACCGATE-3.6 (K), V-ACCGATE-4.6 (K)
/ACCGATE/Heater-6.3V: D-ACCGATE-1.1 (H), D-ACCGATE-2.1 (H), D-ACCGATE-3.1 (H), D-ACCGATE-4.1 (H), D-ACCGATE-5.1 (H), D-ACCGATE-6.1 (H), D-ACCGATE-7.1 (H), D-ACCGATE-8.1 (H), J-ACCGATE-5.10, J-ACCGATE-5.12, V-ACCGATE-1.9 (H), V-ACCGATE-2.9 (H), V-ACCGATE-3.9 (H), V-ACCGATE-4.9 (H), V-ACCGATE-5.9 (H)
/ACCGATE/Heater-GND: D-ACCGATE-1.3 (H), D-ACCGATE-2.3 (H), D-ACCGATE-3.3 (H), D-ACCGATE-4.3 (H), D-ACCGATE-5.3 (H), D-ACCGATE-6.3 (H), D-ACCGATE-7.3 (H), D-ACCGATE-8.3 (H), J-ACCGATE-5.9, J-ACCGATE-5.11, V-ACCGATE-1.1 (H), V-ACCGATE-2.1 (H), V-ACCGATE-3.1 (H), V-ACCGATE-4.1 (H), V-ACCGATE-5.1 (H)
unnamed: C-ACCGATE-1.1, D-ACCGATE-2.4 (A), R-ACCGATE-4.2, V-ACCGATE-1.3 (A)
unnamed: C-ACCGATE-1.2, D-ACCGATE-3.4 (A), D-ACCGATE-4.2 (K)
unnamed: C-ACCGATE-2.1, R-ACCGATE-5.1, V-ACCGATE-1.2 (G2)
unnamed: C-ACCGATE-3.1, D-ACCGATE-4.4 (A), D-ACCGATE-5.2 (K), R-ACCGATE-7.2
unnamed: C-ACCGATE-6.1, R-ACCGATE-14.1, V-ACCGATE-3.2 (G2)
unnamed: C-ACCGATE-9.1, R-ACCGATE-17.1, V-ACCGATE-4.2 (G2)
unnamed: D-ACCGATE-1.2 (K), J-ACCGATE-2.1
unnamed: D-ACCGATE-1.4 (A), R-ACCGATE-1.1, R-ACCGATE-3.2
unnamed: D-ACCGATE-5.4 (A), R-ACCGATE-6.2
unnamed: D-ACCGATE-6.2 (K), R-ACCGATE-9.1, R-ACCGATE-10.2
unnamed: D-ACCGATE-6.4 (A), J-ACCGATE-9.1
unnamed: D-ACCGATE-7.2 (K), R-ACCGATE-11.1, R-ACCGATE-18.2, V-ACCGATE-3.3 (A), V-ACCGATE-4.3 (A)
unnamed: J-ACCGATE1.1, R-ACCGATE-2.2
unnamed: J-ACCGATE-1.1, R-ACCGATE-1.2, SW-ACCGATE-1.2 (B)
unnamed: J-ACCGATE-3.1, SW-ACCGATE-1.1 (A)
unnamed: J-ACCGATE-4.1, SW-ACCGATE-1.3 (C)
unnamed: J-ACCGATE-6.1, R-ACCGATE-6.1
unnamed: J-ACCGATE-7.1, R-ACCGATE-8.2, V-ACCGATE-6.6 (K)
unnamed: J-ACCGATE-8.1, R-ACCGATE-9.2
unnamed: J-ACCGATE-10.1, R-ACCGATE-12.2
unnamed: J-ACCGATE-11.1, R-ACCGATE-13.2
unnamed: J-ACCGATE-12.1, R-ACCGATE-16.2
unnamed: J-ACCGATE-13.1, R-ACCGATE-19.2, V-ACCGATE-7.6 (K)
unnamed: R-ACCGATE-2.1, V-ACCGATE-1.4 (G3)
unnamed: R-ACCGATE-3.1, V-ACCGATE-1.7 (G1)
unnamed: R-ACCGATE-7.1, V-ACCGATE-6.7 (G1)
unnamed: R-ACCGATE-10.1, V-ACCGATE-3.7 (G1)
unnamed: R-ACCGATE-12.1, R-ACCGATE-13.1, R-ACCGATE-15.2
unnamed: R-ACCGATE-15.1, V-ACCGATE-4.7 (G1)
unnamed: R-ACCGATE-16.1, V-ACCGATE-4.4 (G3)
unnamed: R-ACCGATE-18.1, V-ACCGATE-7.7 (G1)

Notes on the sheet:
Switch mounted on the side of the rack.
Control dark for functions 2,3,4,5,6 & 7 during action beat.
